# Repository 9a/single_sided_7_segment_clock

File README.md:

# Single Sided 7 segment clock PCB (optimized for use with ESP D1 Mini/ESP-home)
A pcb design for a 7 segment clock for single sided milled pcbs. Designed with KiCad 10. 

BOM (alternatives are also OK):
- 2x SN74HC595DR 
- 29x 150080RS75000
- 8x 10 Ohm 0805 (or 0603)

See schematic/placement picture for assembly (diode orientation!). The through holes other than for the 5 pin connector need to be connected via jumper wires.

It is designed to be connected to a USB-C ESP8266 D1-mini with a one to one connection via jumper wires to the pins 5V GND D4 D3 D2. Since the pins expose the control pins of the shift registers any microcontroller can be adapted.

For use with ESP home in Homeassistant:
The provided esp_yaml.txt can be copied when creating the device, the cnc_display.h needs to be copied into the esphome directory.

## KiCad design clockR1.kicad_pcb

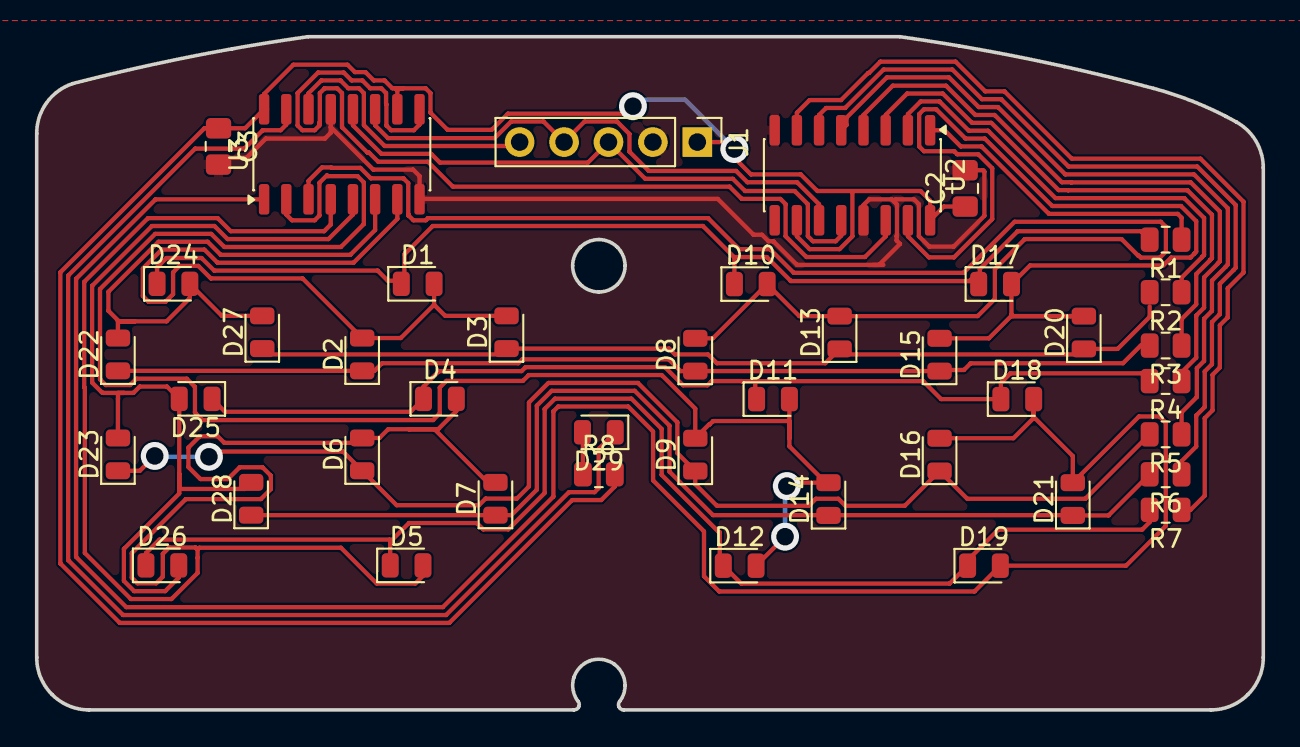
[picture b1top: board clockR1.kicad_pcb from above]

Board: 2 copper layers, 70.1 x 38.5 mm, 42 parts (0 on the bottom side), 30 nets.

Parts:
C2, C3: C; C_0805_2012Metric_Pad1.18x1.45mm_HandSolder
D1, D2, D3, D4, D5, D6, D7, D8, D9, D10, D11, D12, D13, D14, D15, D16, D17, D18, D19, D20, D21, D22, D23, D24, D25, D26, D27, D28, D29: LED; LED_0805_2012Metric
J1: Conn_01x05_Pin; PinHeader_1x05_P2.54mm_Vertical
R1, R2, R3, R4, R5, R6, R7, R8: 100; R_0805_2012Metric
U2, U3: 74HC595; SO-16_3.9x9.9mm_P1.27mm

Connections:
+5V: C2.1, C3.1, J1.1, R8.2, U2.10 (~SRCLR), U2.16 (VCC), U3.10 (~SRCLR), U3.16 (VCC)
/AN_A: D23.2 (A), D25.2 (A), D26.2 (A), D28.2 (A), U3.5 (QF)
/AN_Asec: D22.2 (A), D24.2 (A), D27.2 (A), U3.6 (QG)
/AN_B: D4.2 (A), D5.2 (A), D6.2 (A), D7.2 (A), U3.4 (QE)
/AN_Bsec: D1.2 (A), D2.2 (A), D3.2 (A), U3.7 (QH)
/AN_C: D9.2 (A), D11.2 (A), D12.2 (A), D14.2 (A), U3.2 (QC)
/AN_Csec: D8.2 (A), D10.2 (A), D13.2 (A), U3.3 (QD)
/AN_D: D16.2 (A), D18.2 (A), D19.2 (A), D21.2 (A), U3.1 (QB)
/AN_Dsec: D15.2 (A), D17.2 (A), D20.2 (A), U2.15 (QA)
/CLK: J1.4, U2.11 (SRCLK), U3.11 (SRCLK)
/LATCH: J1.3, U2.12 (RCLK), U3.12 (RCLK)
/SER: J1.5, U3.14 (SER)
/a: D1.1 (K), D10.1 (K), D17.1 (K), D24.1 (K), R1.2
/b: D3.1 (K), D13.1 (K), D20.1 (K), D27.1 (K), R2.2
/c: D7.1 (K), D14.1 (K), D21.1 (K), D28.1 (K), R6.2
/d: D5.1 (K), D12.1 (K), D19.1 (K), D26.1 (K), R7.2
/e: D6.1 (K), D9.1 (K), D16.1 (K), D23.1 (K), R5.2
/f: D2.1 (K), D8.1 (K), D15.1 (K), D22.1 (K), R3.2
/g: D4.1 (K), D11.1 (K), D18.1 (K), D25.1 (K), R4.2
GND: C2.2, C3.2, J1.2, U2.8 (GND), U2.13 (~OE), U3.8 (GND), U3.13 (~OE)
unnamed: D29.2 (A), R8.1
unnamed: D29.1 (K), U3.15 (QA)
unnamed: R1.1, U2.1 (QB)
unnamed: R2.1, U2.2 (QC)
unnamed: R3.1, U2.3 (QD)
unnamed: R4.1, U2.4 (QE)
unnamed: R5.1, U2.5 (QF)
unnamed: R6.1, U2.6 (QG)
unnamed: R7.1, U2.7 (QH)
unnamed: U2.14 (SER), U3.9 (QH')
